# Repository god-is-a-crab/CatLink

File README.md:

# CatLink
This is a GPS tracking solution for cats.

## Overview

There are 3 components of the CatLink system:

- Tracker (collar) - This device tracks the animal's position
- Gateway - This device manages communication with the tracker and the user's phone
- CatLink app - Displays animal position, radio link quality and other information

## Bluetooth Bonding
1. Open the app
2. When it tries to connect to the gateway, it will ask for a passkey to bond
3. Enter the number written on the gateway case
4. Close the app and open it again, the bluetooth connect button should show a green check mark

## How to use

1. Wake up the gateway using the RST button, a white LED will flash to indicate the gateway is pending connection
2. On your phone, turn on location services and open the app
3. Monitor the bluetooth button (number 2 in image), wait for a green check mark to show
4. Press the tracker connect button (number 3 in image), wait for green check mark
5. Wait for tracker position marker (number 5 in image) to update
6. Monitor heartbeat symbol (number 8 in image) to confirm tracker is communicating

## Images

### Collar

### Gateway

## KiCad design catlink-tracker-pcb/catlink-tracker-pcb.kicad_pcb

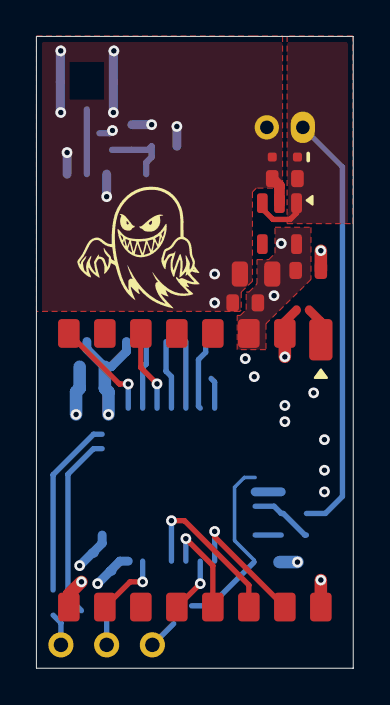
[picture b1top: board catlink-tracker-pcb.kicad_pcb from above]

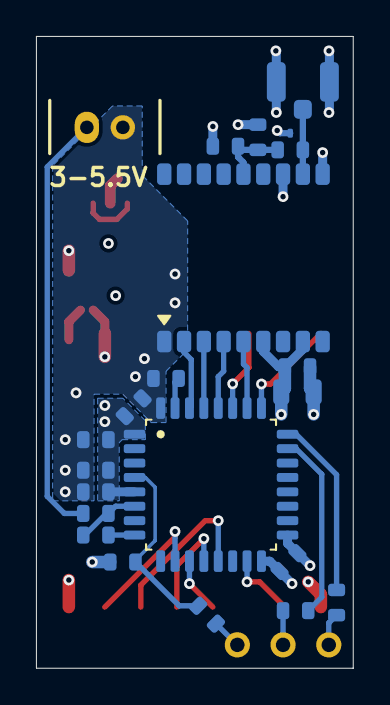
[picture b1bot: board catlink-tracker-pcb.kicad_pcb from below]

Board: 4 copper layers, 17.6 x 35.1 mm, 33 parts (25 on the bottom side), 26 nets.

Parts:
C1: 4u7; C_0603_1608Metric
C2, C3, C6, C10, C12, C13: 100n; C_0603_1608Metric
C4: 10n; C_0603_1608Metric
C5, C7, C8: 1u; C_0603_1608Metric
C9, C11: 10u; C_0805_2012Metric
C14: 100p; C_0603_1608Metric
D1: ESD5Z6.0T1G; D_SOD-523
D2, D3: TPD1E0B04DPY; D_Texas_DPY0002A_0.6x1mm_P0.65mm
J1: S2B-PH-K; JST_PH_S2B-PH-K_1x02_P2.00mm_Horizontal
J2: U.FL; U.FL_Hirose_U.FL-R-SMT-1_Vertical
L1: 82n; L_0603_1608Metric
R1, R2, R3, R4: 10k; R_0603_1608Metric
R5, R6: 100r; R_0603_1608Metric
TP1, TP2, TP3: TestPoint; TestPoint_THT_D1.4mm_Drill0.8mm
U1: STM32L412K8Tx; LQFP-32_7x7mm_P0.8mm
U2: TLV75530PDBV; SOT-23-5
U3: Ai-Thinker-Ra-01S
U4: E108-GN03

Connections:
+3V0: C1.1, C2.1, C3.1, C4.1, C5.1, C8.1, C9.1, C10.1, C11.1, C12.1, U1.1 (VDD), U1.5 (VDDA), U1.17 (VDD), U2.5 (OUT), U3.3 (VDD), U4.6 (V_BCKP), U4.8 (VCC)
/1PPS: U1.28 (PB5), U4.4 (1PPS)
/BOOT0: R1.1, U1.31 (PH3)
/BUSY: U1.15 (PB1), U3.10 (BUSY)
/DIO1: U1.27 (PB4), U3.6 (DIO1)
/DIO3: U1.25 (PA15), U3.8 (DIO3)
/GNSS_RxD: U1.29 (PB6), U4.3 (RxD)
/GNSS_TXD: U1.30 (PB7), U4.2 (TXD)
/LoRa_ANT: D2.1 (A1), U3.1 (ANT)
/MISO: U1.12 (PA6), U3.13 (MISO)
/MOSI: U1.13 (PA7), U3.14 (MOSI)
/ON_OFF: U1.26 (PB3), U4.5 (ON_OFF)
/RF_IN: D3.1 (A1), J2.1 (In), L1.1, U4.11 (RF_IN)
/SCK: U1.11 (PA5), U3.12 (SCK)
/SWCLK: R6.2, TP3.1
/SWDIO: R5.2, TP2.1
/VCC_RF: C13.1, C14.1, L1.2, U4.14 (VCC_RF)
/VIN: C7.1, D1.1 (K), J1.2, R2.1, U2.1 (IN), U2.3 (EN)
/VIN_ADC: R2.2, R3.1, U1.6 (PA0)
/VIN_ADC_DIV_EN: R3.2, U1.8 (PA2)
/~NRST: R4.1, TP1.1
/~NSS: U1.10 (PA4), U3.15 (~NSS)
GND: C1.2, C2.2, C3.2, C4.2, C5.2, C6.2, C7.2, C8.2, C9.2, C10.2, C11.2, C12.2, C13.2, C14.2, D1.2 (A), D2.2 (A2), D3.2 (A2), J1.1, J2.2 (Ext), R1.2, U1.16 (VSS), U1.32 (VSS), U2.2 (GND), U3.2 (GND), U3.9 (GND), U3.16 (GND), U4.1 (GND), U4.10 (GND), U4.12 (GND)
unnamed: C6.1, R4.2, U1.4 (NRST)
unnamed: R5.1, U1.23 (PA13)
unnamed: R6.1, U1.24 (PA14)

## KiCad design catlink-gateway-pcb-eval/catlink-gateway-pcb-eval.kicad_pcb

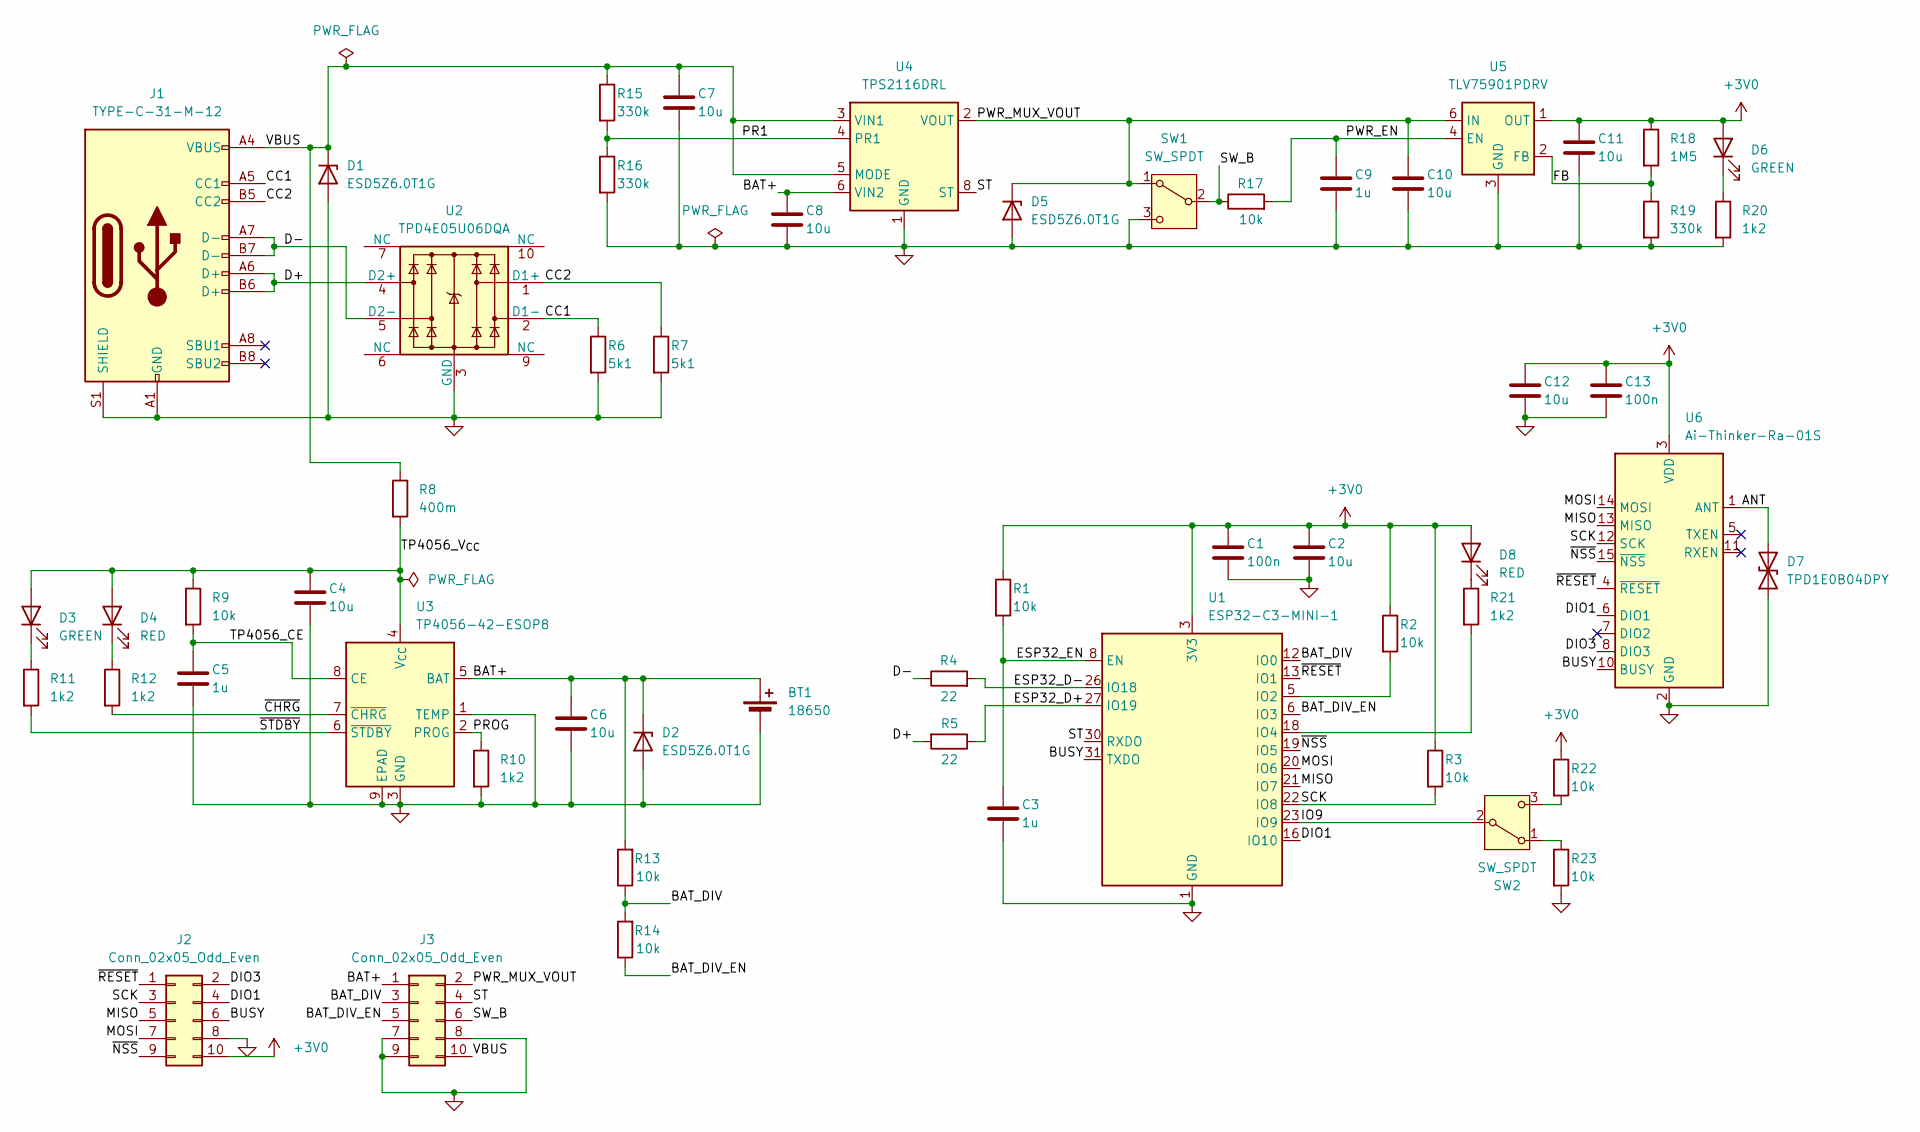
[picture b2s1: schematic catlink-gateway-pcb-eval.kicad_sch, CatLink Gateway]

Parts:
BT1: 18650; BatteryHolder_Keystone_1042_1x18650
C1, C13: 100n; C_0603_1608Metric
C2, C4, C6, C7, C8, C10, C11, C12: 10u; C_0805_2012Metric
C3, C5, C9: 1u; C_0603_1608Metric
D1, D2, D5: ESD5Z6.0T1G; D_SOD-523
D3, D6: GREEN; LED_0805_2012Metric
D4, D8: RED; LED_0805_2012Metric
D7: TPD1E0B04DPY; D_Texas_DPY0002A_0.6x1mm_P0.65mm
J1: TYPE-C-31-M-12; USB_C_Receptacle_HRO_TYPE-C-31-M-12
J2, J3: Conn_02x05_Odd_Even; PinHeader_2x05_P2.54mm_Vertical
R1, R2, R3, R9, R13, R14, R17, R22, R23: 10k; R_0603_1608Metric
R4, R5: 22; R_0603_1608Metric
R6, R7: 5k1; R_0603_1608Metric
R8: 400m; R_1206_3216Metric
R10, R11, R12, R20, R21: 1k2; R_0603_1608Metric
R15, R16, R19: 330k; R_0603_1608Metric
R18: 1M5; R_0603_1608Metric
SW1, SW2: SW_SPDT; SW_Slide_SPDT_Angled_CK_OS102011MA1Q
U1: ESP32-C3-MINI-1
U2: TPD4E05U06DQA; USON-10_2.5x1.0mm_P0.5mm
U3: TP4056-42-ESOP8; SOIC-8-1EP_3.9x4.9mm_P1.27mm_EP2.41x3.3mm
U4: TPS2116DRL; SOT-583-8
U5: TLV75901PDRV; WSON-6-1EP_2x2mm_P0.65mm_EP1x1.6mm
U6: Ai-Thinker-Ra-01S

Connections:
+3V0: C1.1, C2.1, C11.1, C12.1, C13.1, D6.2 (A), D8.2 (A), J2.10, R1.1, R2.1, R3.1, R18.1, R22.1, U1.3 (3V3), U5.1 (OUT), U6.3 (VDD)
/ANT: D7.2 (A2), U6.1 (ANT)
/BAT+: BT1.1 (+), C6.1, C8.1, D2.1 (K), J3.1, R13.2, U3.5 (BAT), U4.6 (VIN2)
/BAT_DIV: J3.3, R13.1, R14.2, U1.12 (IO0)
/BAT_DIV_EN: J3.5, R14.1, U1.6 (IO3)
/BUSY: J2.6, U1.31 (TXDO), U6.10 (BUSY)
/CC1: J1.A5 (CC1), R6.1, U2.2 (D1-)
/CC2: J1.B5 (CC2), R7.1, U2.1 (D1+)
/D+: J1.A6 (D+), J1.B6 (D+), R5.2, U2.4 (D2+)
/D-: J1.A7 (D-), J1.B7 (D-), R4.1, U2.5 (D2-)
/DIO1: J2.4, U1.16 (IO10), U6.6 (DIO1)
/DIO3: J2.2, U6.8 (DIO3)
/ESP32_D+: R5.1, U1.27 (IO19)
/ESP32_D-: R4.2, U1.26 (IO18)
/ESP32_EN: C3.1, R1.2, U1.8 (EN)
/FB: R18.2, R19.1, U5.2 (FB)
/IO9: SW2.2 (B), U1.23 (IO9)
/MISO: J2.5, U1.21 (IO7), U6.13 (MISO)
/MOSI: J2.7, U1.20 (IO6), U6.14 (MOSI)
/PR1: R15.2, R16.1, U4.4 (PR1)
/PROG: R10.1, U3.2 (PROG)
/PWR_EN: C9.1, R17.2, U5.4 (EN)
/PWR_MUX_VOUT: C10.1, D5.1 (K), J3.2, SW1.1 (A), U4.2 (VOUT), U4.7 (VOUT), U5.6 (IN)
/SCK: J2.3, R3.2, U1.22 (IO8), U6.12 (SCK)
/ST: J3.4, U1.30 (RXDO), U4.8 (ST)
/SW_B: J3.6, R17.1, SW1.2 (B)
/TP4056_CE: C5.1, R9.2, U3.8 (CE)
/TP4056_V_{CC}: C4.1, D3.2 (A), D4.2 (A), R8.2, R9.1, U3.4 (V_{CC})
/VBUS: C7.1, D1.1 (K), J1.A4 (VBUS), J1.A9 (VBUS), J1.B4 (VBUS), J1.B9 (VBUS), J3.10, R8.1, R15.1, U4.3 (VIN1), U4.5 (MODE)
/~CHRG: R12.2, U3.7 (~CHRG)
/~NSS: J2.9, U1.19 (IO5), U6.15 (~NSS)
/~RESET: J2.1, U1.13 (IO1), U6.4 (~RESET)
/~STDBY: R11.2, U3.6 (~STDBY)
GND: BT1.2 (-), C1.2, C2.2, C3.2, C4.2, C5.2, C6.2, C7.2, C8.2, C9.2, C10.2, C11.2, C12.2, C13.2, D1.2 (A), D2.2 (A), D5.2 (A), D7.1 (A1), J1.A1 (GND), J1.A12 (GND), J1.B1 (GND), J1.B12 (GND), J1.S1 (SHIELD), J2.8, J3.7, J3.8, J3.9, R6.2, R7.2, R10.2, R16.2, R19.2, R20.2, R23.2, SW1.3 (C), U1.1 (GND), U1.2 (GND), U1.11 (GND), U1.14 (GND), U1.36 (GND), U1.37 (GND), U1.38 (GND), U1.39 (GND), U1.40 (GND), U1.41 (GND), U1.42 (GND), U1.43 (GND), U1.44 (GND), U1.45 (GND), U1.46 (GND), U1.47 (GND), U1.48 (GND), U1.49 (GND), U1.50 (GND), U1.51 (GND), U1.52 (GND), U1.53 (GND), U2.3 (GND), U2.8 (GND), U3.1 (TEMP), U3.3 (GND), U3.9 (EPAD), U4.1 (GND), U5.3 (GND), U5.7 (GND), U6.2 (GND), U6.9 (GND), U6.16 (GND)
unnamed: D3.1 (K), R11.1
unnamed: D4.1 (K), R12.1
unnamed: D6.1 (K), R20.1
unnamed: D8.1 (K), R21.1
unnamed: R23.1, SW2.1 (A)
unnamed: R22.2, SW2.3 (C)
unnamed: R2.2, U1.5 (IO2)
unnamed: R21.2, U1.18 (IO4)

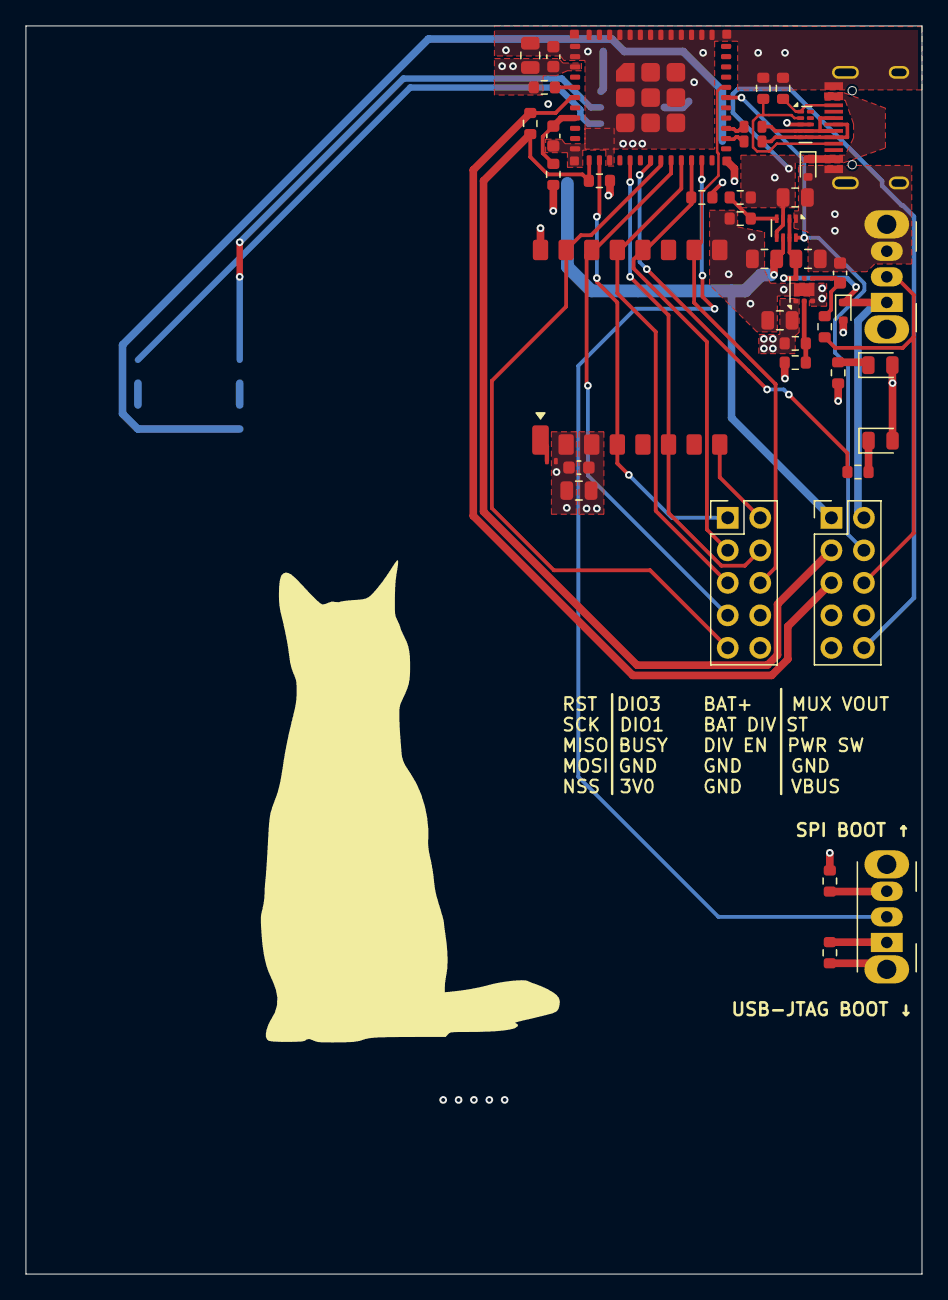
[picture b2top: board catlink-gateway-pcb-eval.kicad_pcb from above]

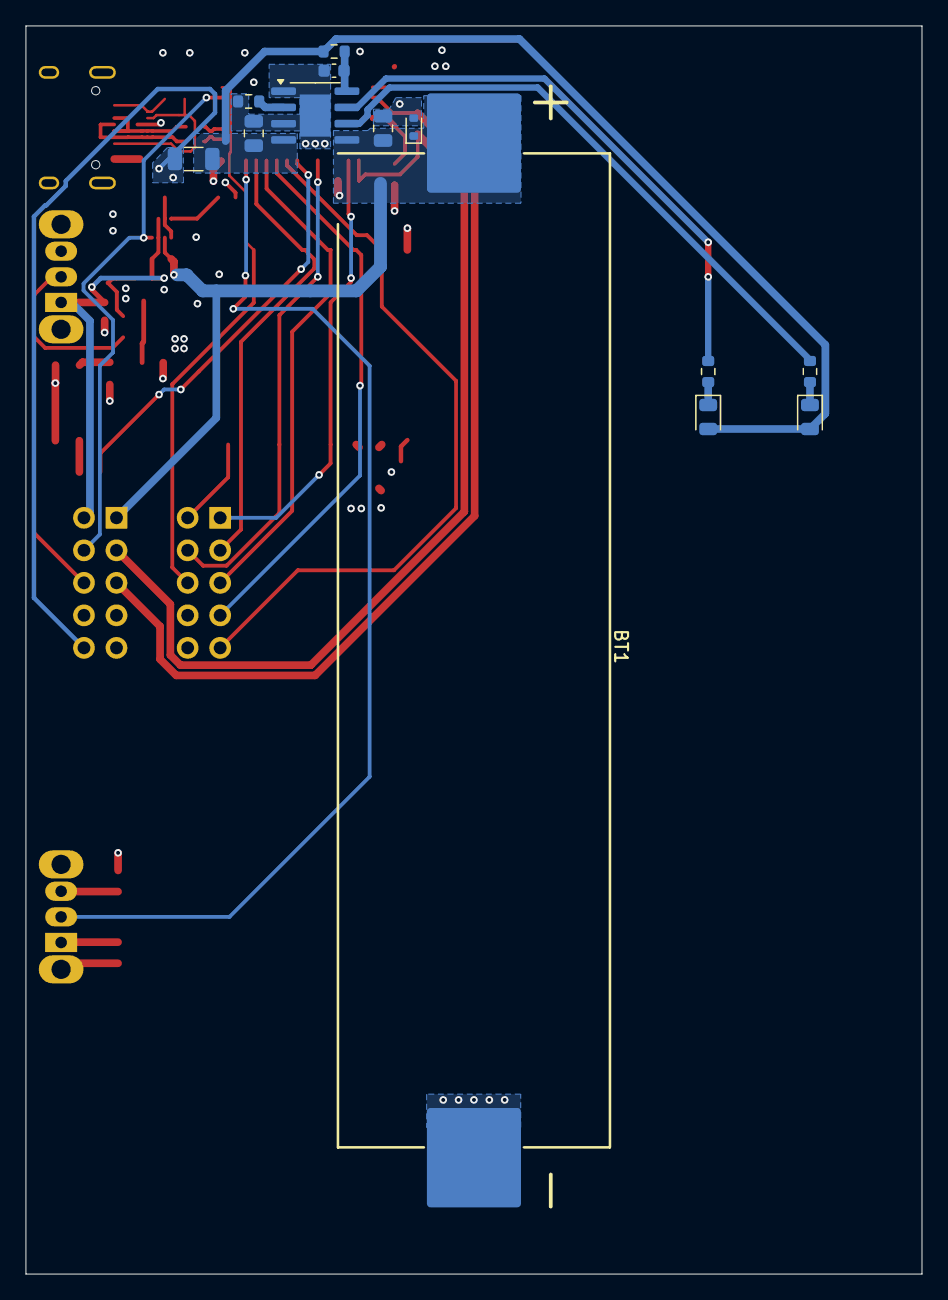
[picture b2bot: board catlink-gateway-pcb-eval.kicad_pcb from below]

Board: 4 copper layers, 70.0 x 97.5 mm, 56 parts (13 on the bottom side), 42 nets.

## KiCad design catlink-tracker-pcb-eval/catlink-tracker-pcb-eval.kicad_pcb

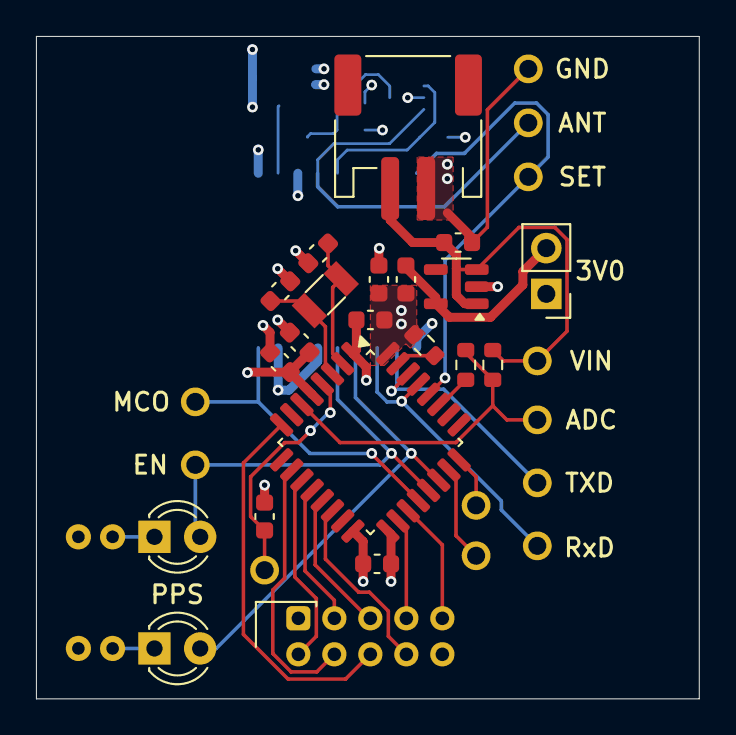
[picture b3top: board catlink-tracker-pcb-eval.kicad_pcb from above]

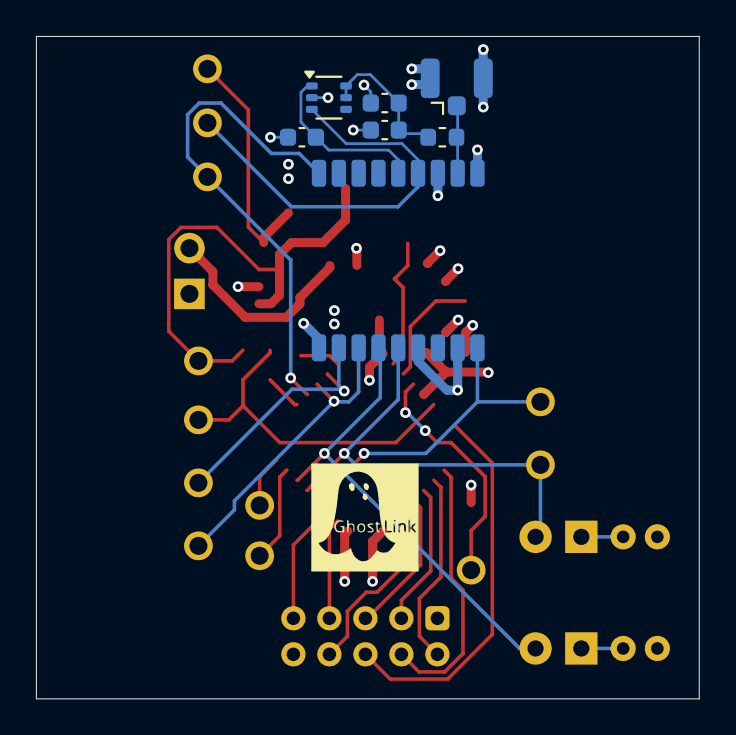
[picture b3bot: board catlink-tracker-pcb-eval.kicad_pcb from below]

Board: 4 copper layers, 36.8 x 36.8 mm, 42 parts (7 on the bottom side), 32 nets.

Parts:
3V0: Jumper; PinHeader_1x02_P2.54mm_Vertical
ADC: TestPoint
ANT: TestPoint
C1: 4u7; C_0603_1608Metric
C2, C3, C6: 100n; C_0603_1608Metric
C4, C13: 10n; C_0603_1608Metric
C5, C9, C10, C11, C12: 1u; C_0603_1608Metric
C7, C8: 18p; C_0603_1608Metric
D1: LED; LED_D3.0mm
EN: TestPoint
GND: TestPoint
J1: S2B-PH-SM4; JST_PH_S2B-PH-SM4-TB_1x02-1MP_P2.00mm_Horizontal
J2: S10B-PHDSS; JST_PHD_S10B-PHDSS_2x05_P2.00mm_Horizontal
J3: U.FL; U.FL_Hirose_U.FL-R-SMT-1_Vertical
L1: 68nH; L_0603_1608Metric
MCO: TestPoint
PPS: LED; LED_D3.0mm
R1, R2, R3: 10k; R_0603_1608Metric
R4, R5: R; R_Axial_DIN0204_L3.6mm_D1.6mm_P1.90mm_Vertical
RxD: TestPoint
SET: TestPoint
TP1, TP2, TP3: TestPoint
TXD: TestPoint
U1: STM32L412K8Tx; LQFP-32_7x7mm_P0.8mm
U2: TLV75530PDBV; SOT-23-5
U3: E108-GN03
U4: TPS22919DCKR; SOT-363_SC-70-6
VIN: TestPoint
Y1: ABS07-32.768KHZ; Crystal_SMD_3215-2Pin_3.2x1.5mm

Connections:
+3.0V: 3V0.1, C1.1, C2.1, C3.1, C4.1, C5.1, J2.10, U1.1 (VDD), U1.5 (VDDA), U1.17 (VDD), U3.6 (V_BCKP), U3.8 (VCC)
/BOOT0: R1.2, U1.31 (PH3)
/GNSS_1PPS: PPS.2 (A), U1.22 (PA12), U3.4 (1PPS)
/GNSS_ANT_ON: ANT.1, U3.13 (ANT_ON), U4.3 (ON)
/GNSS_MODEL_SET: SET.1, U1.28 (PB5), U3.18 (MODEL_SET)
/GNSS_ON_OFF: D1.2 (A), EN.1, U1.21 (PA11), U3.5 (ON_OFF)
/GNSS_RESET_N: MCO.1, U1.20 (PA10), U3.9 (RESET_N)
/GNSS_RF_IN: J3.1 (In), L1.1, U3.11 (RF_IN)
/GNSS_RxD: RxD.1, U1.29 (PB6), U3.3 (RxD)
/GNSS_TXD: TXD.1, U1.30 (PB7), U3.2 (TXD)
/GNSS_VCC_RF: C11.1, U3.14 (VCC_RF), U4.1 (VIN)
/NRST: C6.2, TP1.1, U1.4 (NRST)
/OSC32_IN: C7.2, U1.2 (PC14), Y1.2
/OSC32_OUT: C8.2, U1.3 (PC15), Y1.1
/SWCLK: TP3.1, U1.24 (PA14)
/SWDIO: TP2.1, U1.23 (PA13)
/SX126x_BUSY: J2.4, U1.10 (PA4)
/SX126x_DIO1: J2.6, U1.8 (PA2)
/SX126x_DIO3: J2.9, U1.19 (PA9)
/SX126x_MISO: J2.3, U1.12 (PA6)
/SX126x_MOSI: J2.5, U1.13 (PA7)
/SX126x_NSS: J2.8, U1.14 (PB0)
/SX126x_REST: J2.7, U1.18 (PA8)
/SX126x_SCK: J2.2, U1.11 (PA5)
/VIN_ADC: ADC.1, R2.1, R3.2, U1.6 (PA0)
/VIN_ADC_DIV_EN: R3.1, U1.27 (PB4)
/V_{IN}: C9.1, J1.2, R2.2, U2.1 (IN), U2.3 (EN), VIN.1
GND: C1.2, C2.2, C3.2, C4.2, C5.2, C6.1, C7.1, C8.1, C9.2, C10.2, C11.2, C12.2, C13.2, GND.1, J1.1, J2.1, J3.2 (Ext), R1.1, R4.2, R5.2, U1.16 (VSS), U1.32 (VSS), U2.2 (GND), U3.1 (GND), U3.10 (GND), U3.12 (GND), U4.2 (GND)
unnamed: D1.1 (K), R4.1
unnamed: PPS.1 (K), R5.1
unnamed: 3V0.2, C10.1, U2.5 (OUT)
unnamed: C12.1, C13.1, L1.2, U4.5 (QOD), U4.6 (VOUT)

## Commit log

2025-08-26 Initial
2025-08-29 Add .gitattributes
2025-10-12 Update gitignore
2025-10-15 v0.2
2025-10-15 v0.1
2025-10-21 Add BoM for tracker
2025-10-21 Changed logo, added pin 1 silkscreen for ESD diode
2025-12-21 Added state LED and IO9 switch
2025-12-21 Tracker pcb production, gateway eval v0.2 production
2026-01-02 Add catlink-gateway-firmware
2026-01-02 Add catlink_app
2026-01-02 Idle disconnect based on subscriptions, fix oneplus disconnect bug
2026-01-19 Port
2026-01-19 Production pinout
2026-02-16 Increase tracker container
2026-02-20 Add heartbeat indicator to app
2026-02-20 Gateway firmware: fix RSSI overflow, and undivide vbat
2026-02-22 Add enclosure 3D models
2026-02-22 Gateway enclosure
2026-02-22 Update docs
2026-02-22 Take link_ctrl_val mutex for no_subscription check
2026-02-23 Add ble bonding instructions
2026-02-23 Compile gateway-firmware for release mode
2026-02-23 Fix SNR overflow bug in app
2026-02-23 Change tracker signal quality ranges
2026-02-23 Change wake-up interval to 40s
2026-02-27 Power measurement plots
